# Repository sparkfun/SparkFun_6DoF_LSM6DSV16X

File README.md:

# SparkFun 6DoF - LSM6DSV16X (Qwiic)
========================================

<table class="table table-hover table-striped table-bordered">
    <tr>
        <th class="text-center"> 
        </th>
        <th class="text-center">
        </th>
    </tr>
    <tr align="center">
        <td></td>
        <td></td>
    </tr>
    <tr align="center">
        <td><a href="https://www.sparkfun.com/products/21325">SparkFun 6DoF - LSM6DSV16X (Qwiic)</a></td>
        <td><a href="https://www.sparkfun.com/products/21336">SparkFun Micro 6DoF - LSM6DSV16X (Qwiic)</a></td>
    </tr>
</table>

Looking for an extremely accurate way to detect motion utilizing AI? We've got you covered with the Qwiic-enabled, SparkFun LSM6DSV16X 6DoF IMU Breakout and the SparkFun Micro 6DoF - LSM6DSV16X (Qwiic). The LSM6DSV16X Breakout is a high-performance, low-power 6-axis IMU, featuring a 3-axis digital accelerometer, and a 3-axis digital gyroscope, with a triple core for processing acceleration and angular rate data on three separate channels (user interface, OIS, and EIS) with dedicated configuration, processing, and filtering. All this functionality comes in our standard 1in. x 1in. Qwiic form factor and will seamlessly integrate into your Qwiic-based projects. However, we still routed the I<sup>2</sup>C signals out to a set of 0.1in.-spaced pins for users who prefer a soldered connection.

The triple core of the LSM6DSV16X enables processes in edge computing, leveraging embedded advanced dedicated features such as a finite state machine (FSM) for configurable motion tracking and a machine learning core (MLC) for contextual awareness with exportable AI features for IoT applications. 

Additionally, Qvar (electric charge variation detection) is embedded in the LSM6DSV16X for user interface functions like tap, double tap, triple tap, long press, or L/R – R/L swipe.

Repository Contents
-------------------

* **/Documentation** - Data sheets, additional product information
* **/Hardware** - Eagle design files (.brd, .sch)

Documentation
--------------
* **[Library](https://github.com/sparkfun/SparkFun_LSM6DSV16X_Arduino_Library)** - Arduino library for the SparkFun 6DoF - LSM6DSV16X (Qwiic) and the SparkFun Micro 6DoF - LSM6DSV16X (Qwiic). 
* **[Hookup Guide](https://learn.sparkfun.com/tutorials/sparkfun-6dof-lsm6dsv16x-qwiic-hookup-guide)** - Basic hookup guide for the SparkFun 6DoF - LSM6DSV16X (Qwiic) and the SparkFun Micro 6DoF - LSM6DSV16X (Qwiic).

License Information
-------------------

This product is _**open source**_! 

Please review the LICENSE.md file for license information. 

If you have any questions or concerns on licensing, please contact technical support on our [SparkFun forums](https://forum.sparkfun.com/viewforum.php?f=152).

Distributed as-is; no warranty is given.

- Your friends at SparkFun.

_<COLLABORATION CREDIT>_

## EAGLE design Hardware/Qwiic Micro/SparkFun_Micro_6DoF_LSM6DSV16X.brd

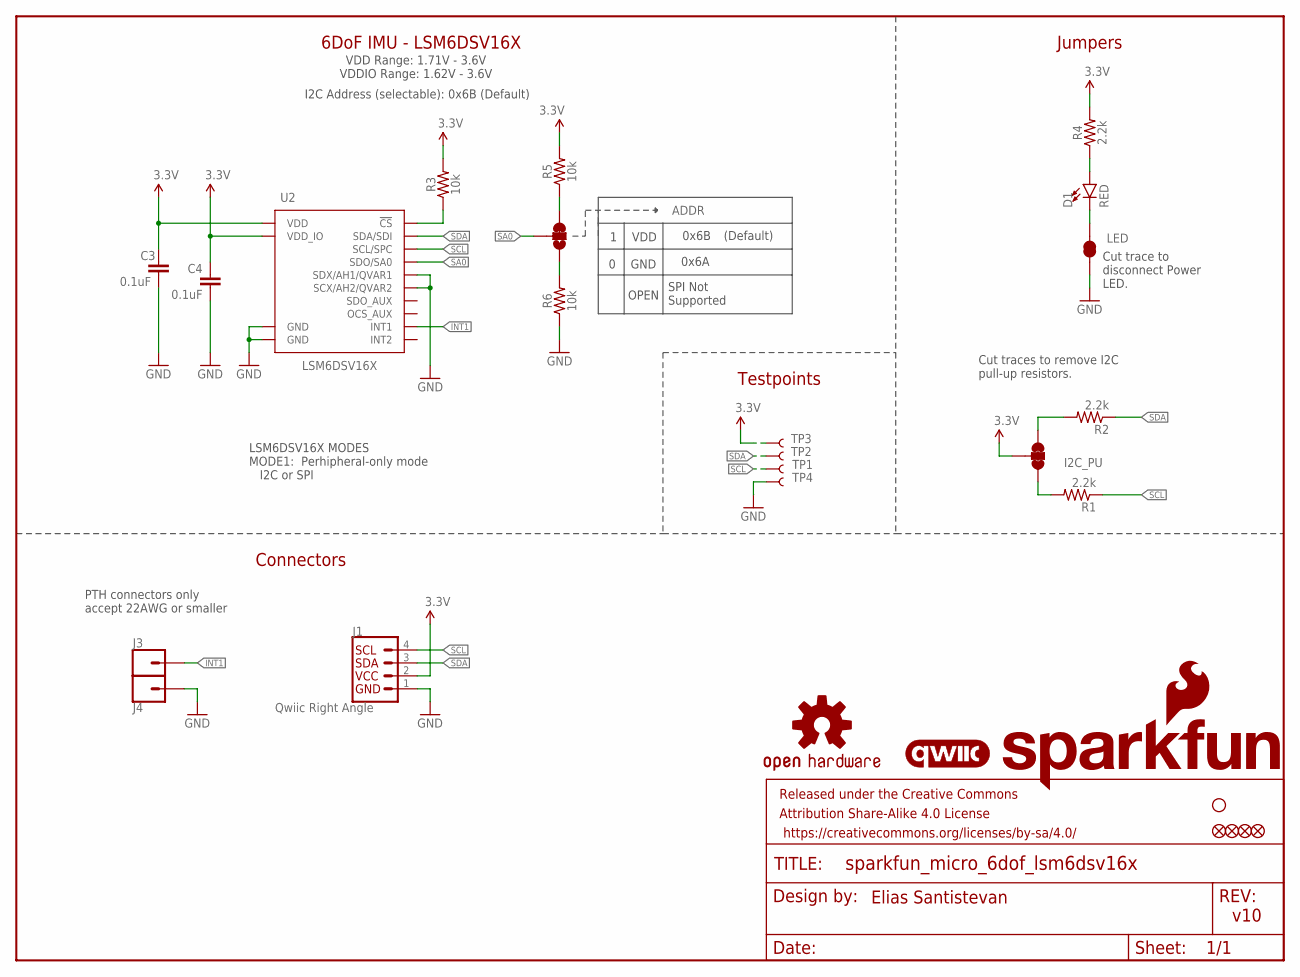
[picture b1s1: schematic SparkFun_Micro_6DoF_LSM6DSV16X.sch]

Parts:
ADDR: JUMPER-SMT_3_1-NC_TRACE_SILK; SMT-JUMPER_3_1-NC_TRACE_SILK
C3, C4: 0.1uF; 0402-TIGHT
D1: RED; LED-0402
FD1, FD2: FIDUCIALUFIDUCIAL; FIDUCIAL-MICRO
FID1, FID2: FIDUCIALUFIDUCIAL; FIDUCIAL-MICRO
FRAME1: FRAME-LETTER; CREATIVE_COMMONS
I2C_PU: S_MODE; SMT-JUMPER_3_2-NC_TRACE_SILK
J1: Qwiic Right Angle; JST04_1MM_RA
J3, J4: CONN_01_1MM; 1X01_1MM_NO_SILK
LED: JUMPER-SMT_2_NC_TRACE_SILK; SMT-JUMPER_2_NC_TRACE_SILK
LOGO1: QWIIC_LOGO_3MM; QWIIC_3MM
LOGO2: OSHW-LOGOMINI; OSHW-LOGO-MINI
LOGO3: SFE_LOGO_NAME_FLAMEBLANK; BLANK
R1, R2, R4: 2.2k; 0402-TIGHT
R3, R5, R6: 10k; 0402-TIGHT
STANDOFF1: STAND-OFFTIGHT; STAND-OFF-TIGHT
TP1, TP2, TP3, TP4: TEST-POINT3; PAD.03X.03
U2: LSM6DSV16X; LGA-14L

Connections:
3.3V: C3.1, C4.1, I2C_PU.2, J1.2, R3.2, R4.2, R5.2, TP3.1, U2.P5 (VDD_IO), U2.P8 (VDD)
GND: C3.2, C4.2, J1.1, J4.1, LED.1, R6.1, TP4.1, U2.P2 (SDX/AH1/QVAR1), U2.P3 (SCX/AH2/QVAR2), U2.P6 (GND), U2.P7 (GND)
INT1: J3.1, U2.P4 (INT1)
unnamed: ADDR.3, R5.1
unnamed: D1.A, R4.1
unnamed: D1.C, LED.2
unnamed: R3.1, U2.P12 (!CS!)
unnamed: I2C_PU.1, R1.2
unnamed: I2C_PU.3, R2.2
unnamed: ADDR.1, R6.2
SA0: ADDR.2, U2.P1 (SDO/SA0)
SCL: J1.4, R1.1, TP1.1, U2.P13 (SCL/SPC)
SDA: J1.3, R2.1, TP2.1, U2.P14 (SDA/SDI)

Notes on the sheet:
6DoF IMU - LSM6DSV16X
Cut traces to remove I2C pull-up resistors.
LSM6DSV16X MODES MODE1: Perhipheral-only mode I2C or SPI
VDD Range: 1.71V - 3.6V VDDIO Range: 1.62V - 3.6V
v10
Jumpers
Cut trace to disconnect Power LED.
Connectors
VDD
GND
OPEN
0x6B
0x6A
Elias Santistevan
SPI Not Supported
Testpoints
(Default)
I2C Address (selectable): 0x6B (Default)
PTH connectors only accept 22AWG or smaller

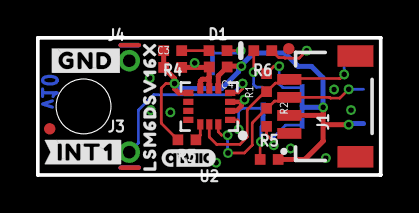
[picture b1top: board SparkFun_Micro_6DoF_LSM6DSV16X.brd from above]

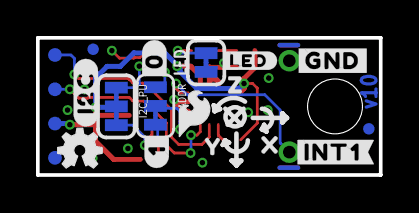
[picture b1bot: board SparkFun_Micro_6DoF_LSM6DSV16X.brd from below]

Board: 2 copper layers, 19.1 x 7.6 mm, 42 parts (20 on the bottom side), 13 nets.

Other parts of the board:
U$1: #0#4
U$2: #1#4
U$3: #LED#2121
U$4, U$10: #GND#4
U$5: #INT1#0
U$6: LSM6DSV16X31
U$7: X2114
U$8: Y2115
U$9: Z2116
U$11: #INT1#2
U$12: #I2C#4
U$29: SFE_LOGO_FLAME_.1

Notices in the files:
parts and their libraries:
SparkFun-Aesthetics: Licensing: Creative Commons ShareAlike 4.0 International - https://creativecommons.org/licenses/by-sa/4.0
SparkFun-Aesthetics: Released under the Creative Commons Attribution Share-Alike 4.0 License
SparkFun-Aesthetics: https://creativecommons.org/licenses/by-sa/4.0
